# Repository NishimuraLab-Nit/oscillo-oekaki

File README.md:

# オシロお絵描き

## About  
オシロスコープで絵を描く

## Usage  
素材をconverter/originalDataに入れる。  
ffmpegを使って動画や画像を256x256pixに変換する。  
動画の場合はフレームレートを指定して画像にする。  
・静止画の場合  
`ffmpeg -i "画像.png" -s 256x256 images/%05d.png`  
・動画の場合  
`ffmpeg -i "ビデオ.mp4" -s 256x256 -r 24 images/%05d.png`  

エッジ検出する。  
`python3 convert.py <ファイル名>`  

回路を組むか基板を積む。  

コンパイルする。  
`gcc -o <paint or movie> oscillo-<paint or movie>.c -lpigpio`  

描画する。  
・静止画の場合  
`sudo ./paint`  
・動画の場合  
`sudo ./movie`  
実行すると、入力ウィザードになるので、ファイル名、フレームレート(動画の場合)を入力する。  

## KiCadプロジェクトについて  
Raspberry Pi Hatを作るプロジェクト。  
ブレボ上で組んでもいいが、これを発注して楽できる。

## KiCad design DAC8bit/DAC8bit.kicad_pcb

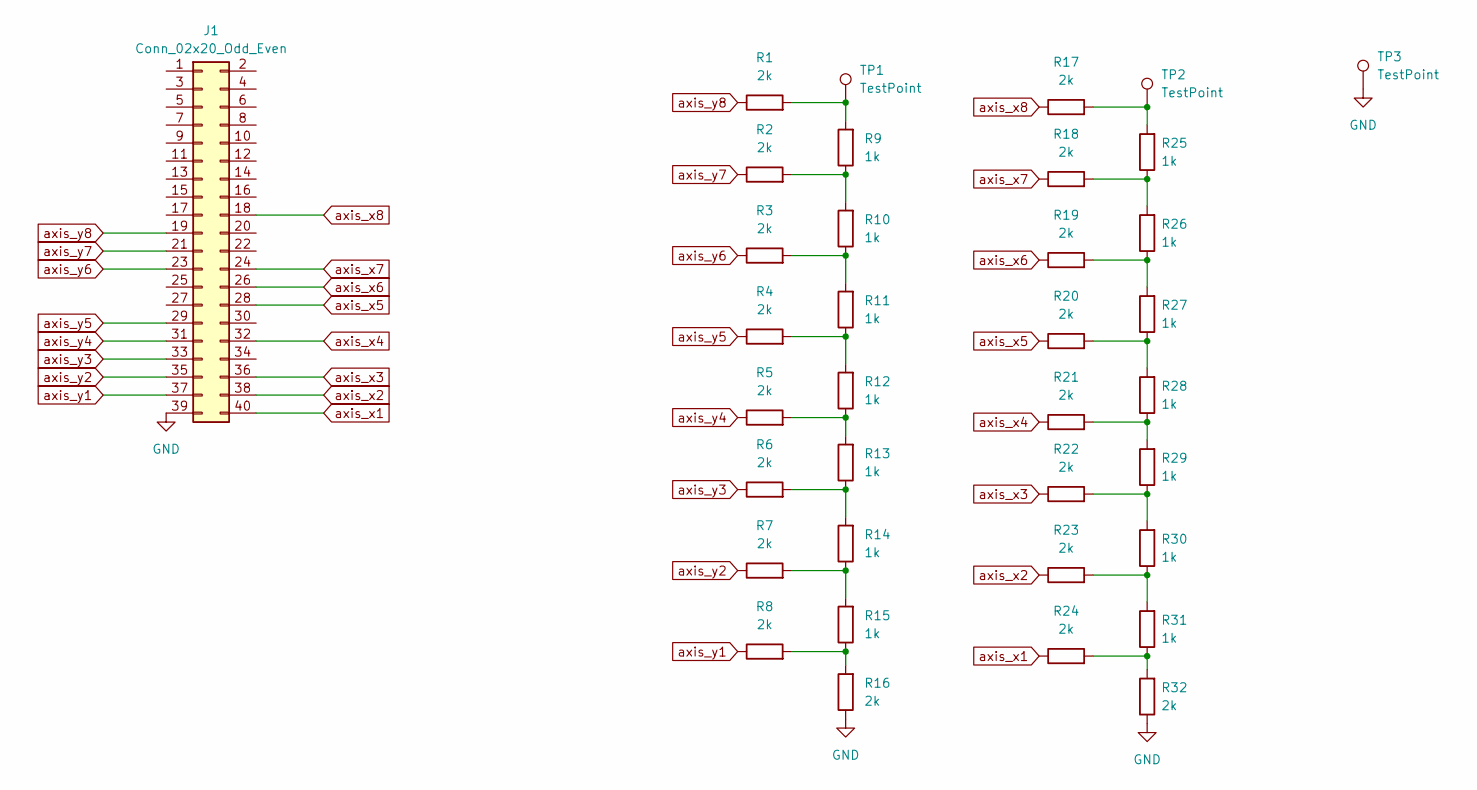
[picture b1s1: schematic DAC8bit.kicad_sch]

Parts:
J1: Conn_02x20_Odd_Even; PinHeader_2x20_P2.54mm_Vertical
R1, R2, R3, R4, R5, R6, R7, R8, R16, R17, R18, R19, R20, R21, R22, R23, R24, R32: 2k; R_Axial_DIN0207_L6.3mm_D2.5mm_P7.62mm_Horizontal
R9, R10, R11, R12, R13, R14, R15, R25, R26, R27, R28, R29, R30, R31: 1k; R_Axial_DIN0207_L6.3mm_D2.5mm_P7.62mm_Horizontal
TP1, TP2, TP3: TestPoint; TestPoint_THTPad_D2.5mm_Drill1.2mm

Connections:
GND: J1.39, R16.1, R32.1, TP3.1
unnamed: R1.2, R9.2, TP1.1
unnamed: R3.2, R10.1, R11.2
unnamed: R2.2, R9.1, R10.2
unnamed: R4.2, R11.1, R12.2
unnamed: R5.2, R12.1, R13.2
unnamed: R6.2, R13.1, R14.2
unnamed: R7.2, R14.1, R15.2
unnamed: R8.2, R15.1, R16.2
unnamed: R17.2, R25.2, TP2.1
unnamed: R18.2, R25.1, R26.2
unnamed: R19.2, R26.1, R27.2
unnamed: R20.2, R27.1, R28.2
unnamed: R21.2, R28.1, R29.2
unnamed: R22.2, R29.1, R30.2
unnamed: R23.2, R30.1, R31.2
unnamed: R24.2, R31.1, R32.2
axis_x1: J1.40, R24.1
axis_x2: J1.38, R23.1
axis_x3: J1.36, R22.1
axis_x4: J1.32, R21.1
axis_x5: J1.28, R20.1
axis_x6: J1.26, R19.1
axis_x7: J1.24, R18.1
axis_x8: J1.18, R17.1
axis_y1: J1.37, R8.1
axis_y2: J1.35, R7.1
axis_y3: J1.33, R6.1
axis_y4: J1.31, R5.1
axis_y5: J1.29, R4.1
axis_y6: J1.23, R3.1
axis_y7: J1.21, R2.1
axis_y8: J1.19, R1.1

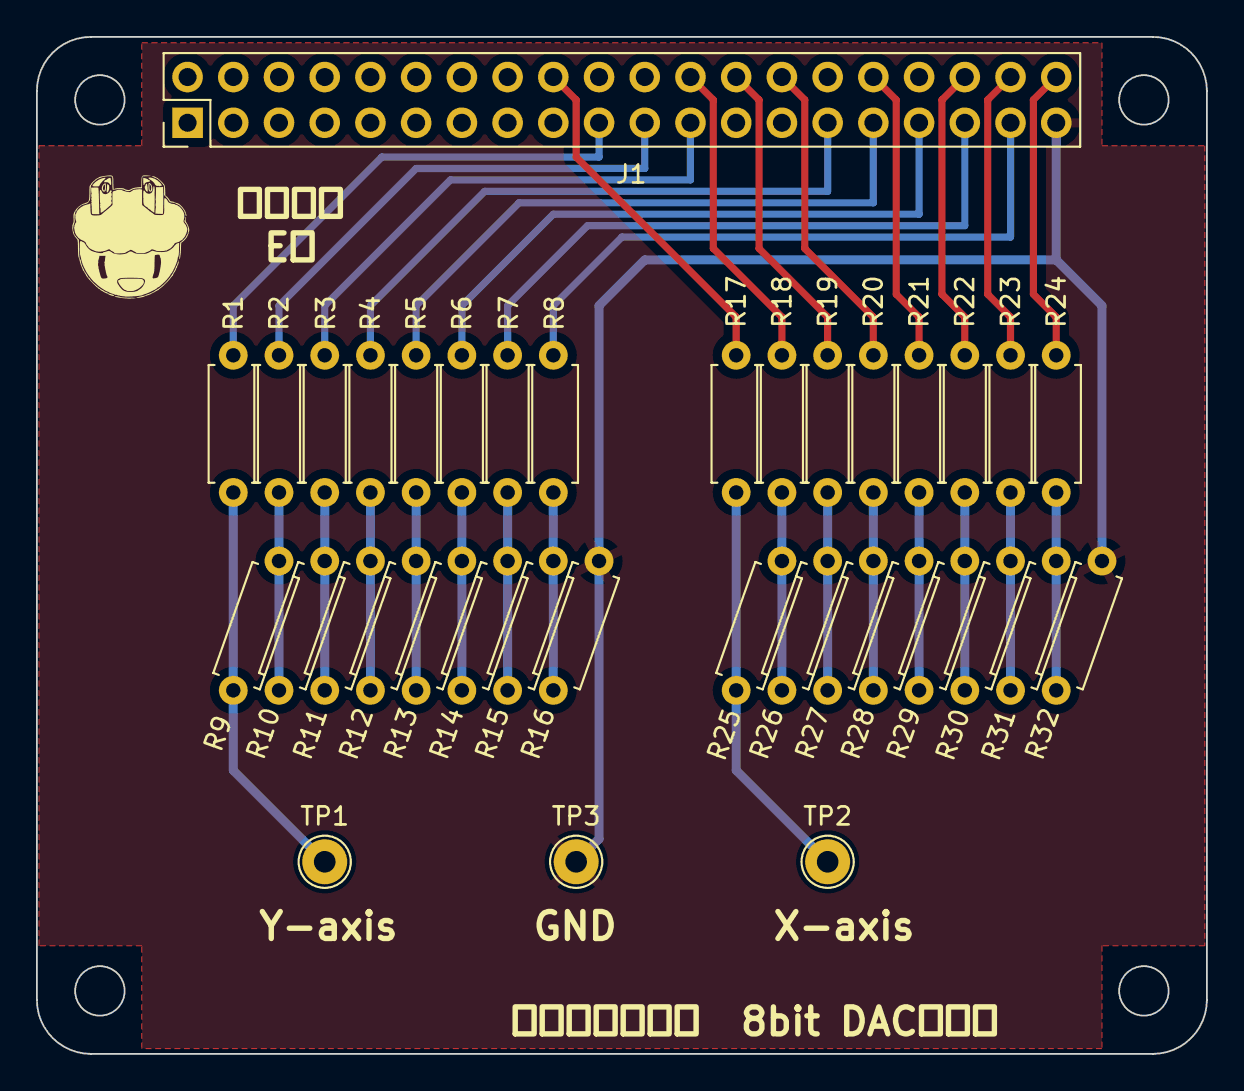
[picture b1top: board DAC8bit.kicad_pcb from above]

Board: 2 copper layers, 65.0 x 56.5 mm, 36 parts (0 on the bottom side), 33 nets.

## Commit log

2024-02-19 readme追加
2024-02-19 コンパイルオプション変更
2024-02-19 変換コマンド修正
2024-02-19 kicadプロジェクトに関して追記
